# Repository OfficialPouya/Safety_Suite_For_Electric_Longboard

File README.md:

# Safety Suite For Electric Longboard
This is my Senior Design (ECE 445) Project

The goal of the project is to increase Safety for electric longboard users. To find out more about the project, feel free to watch the presentation, demos, and the rest of this repository. This project would not have been possible without the help of Alex and Patrick. 

Best Overall Project Winner (Spring 2021)
-----
Best project out of 72 teams/projects

$1500 Award

Contributors
-----
[Pouya Akbarzadeh](https://github.com/OfficialPouya)

[Alexander Krysl](https://github.com/axkrysl47)

[Patrick Stach](https://github.com/pat-stach) 

Demo
-----
[Demo Videos](https://www.youtube.com/playlist?list=PLA1k06jt2lX-8_wawuwcJB9zIEW_f2nJa)

Presentation
-----
[Brief Presentaion](https://www.youtube.com/watch?v=MWs525hmZTg)

Final Results
-----

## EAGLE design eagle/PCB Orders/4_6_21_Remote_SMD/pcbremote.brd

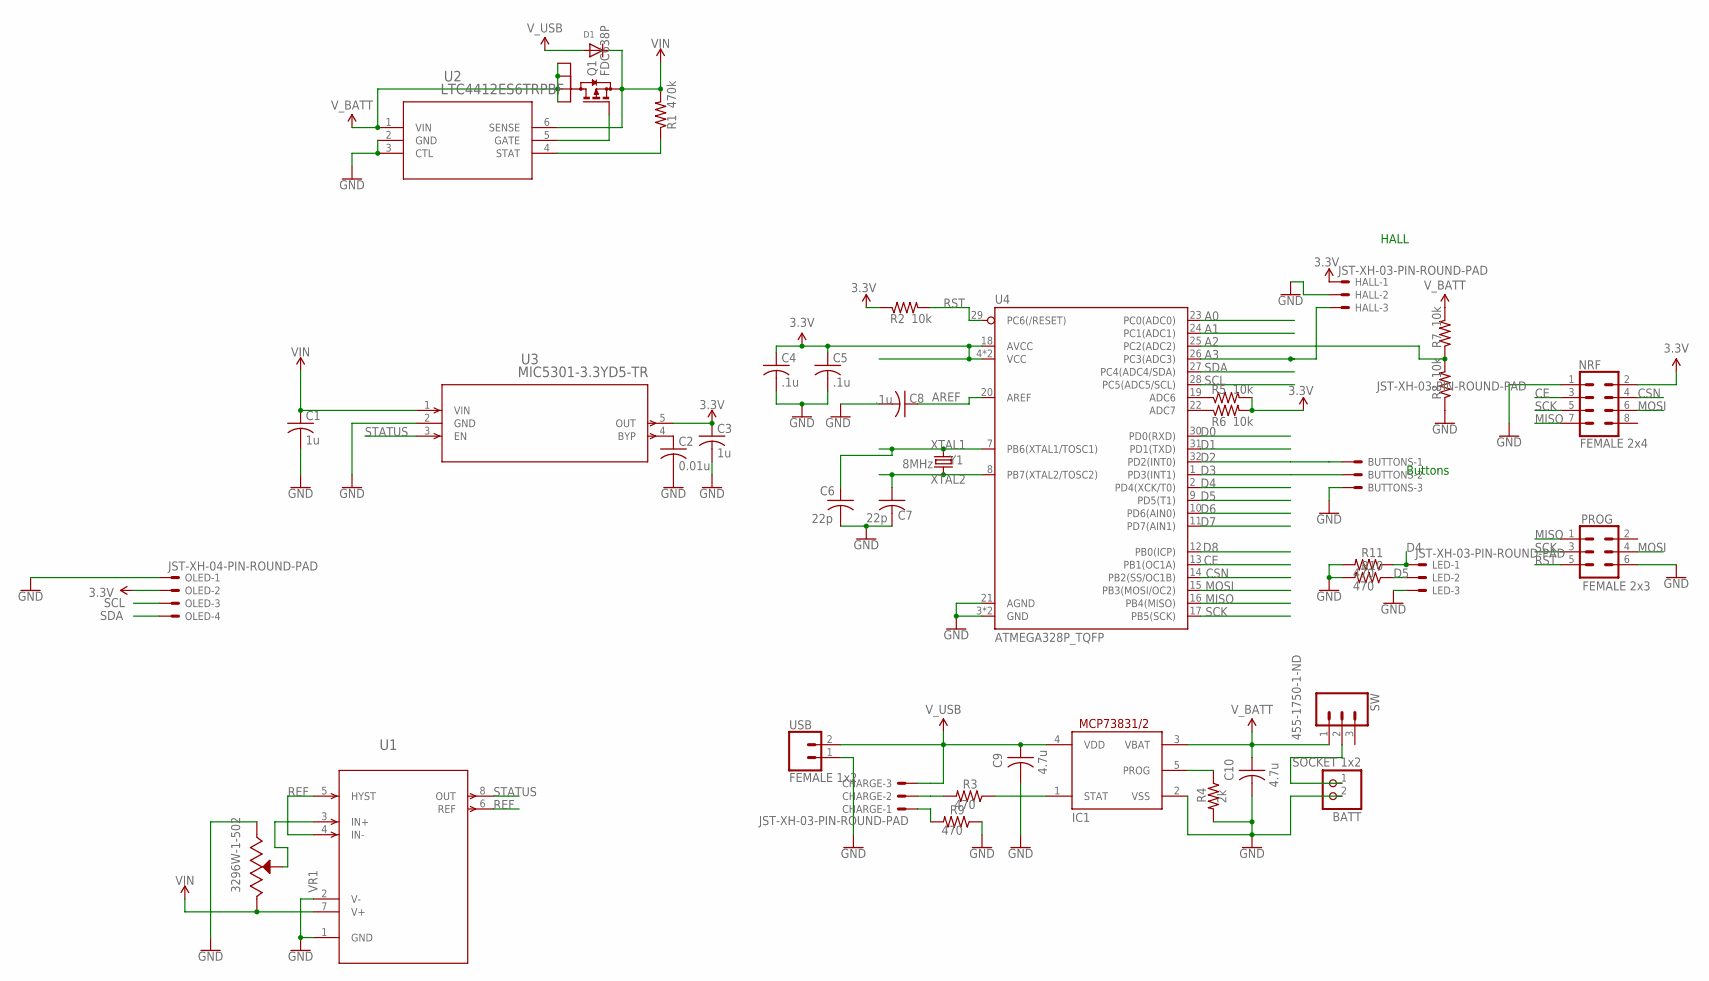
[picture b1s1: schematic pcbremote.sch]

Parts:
BATT: SOCKET 1x2; JST-PH-2-THM
BUTTONS: JST-XH-03-PIN-ROUND-PAD; JST-XH-03-PACKAGE-ROUND-PAD
C1, C3: 1u; C0805
C2: 0.01u; C0805
C4, C5, C8: .1u; C0805
C6, C7: 22p; C0805
C9, C10: 4.7u; C0805
CHARGE: JST-XH-03-PIN-ROUND-PAD; JST-XH-03-PACKAGE-ROUND-PAD
D1: DIODESOD-123; SOD-123
HALL: JST-XH-03-PIN-ROUND-PAD; JST-XH-03-PACKAGE-ROUND-PAD
IC1: MCP73831/OT; SOT23-5L
LED: JST-XH-03-PIN-ROUND-PAD; JST-XH-03-PACKAGE-ROUND-PAD
NRF: FEMALE 2x4; 2X4
OLED: JST-XH-04-PIN-ROUND-PAD; JST-XH-04-PACKAGE-ROUND-PAD
PROG: FEMALE 2x3; 2X3
Q1: FDC638P; SSOT-6
R1: 470k; R0805
R2, R5, R6, R7, R8: 10k; R0805
R3, R9, R10, R11: 470; R0805
R4: 2k; R0805
SW: 455-1750-1-ND; 1X03
U1: LTC1540CS8PBF; SO-8_S_LIT
U2: LTC4412ES6TRPBF; TSOT-23_S6_LIT
U3: MIC5301-3.3YD5-TR; TSOT-23-5_D5_MCH
U4: ATMEGA328P_TQFP; TQFP32-08
USB: FEMALE 1x2; 1X02
VR1: 3296W-1-502; TRIM_3296W-1-502
Y1: 8MHz; CRYSTAL-SMD-5X3.2-4PAD

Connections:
3.3V: C3.1, C4.1, C5.1, HALL.1, NRF.2, OLED.2, R2.1, R5.2, R6.2, U3.5 (OUT), U4.4 (VCC), U4.6 (VCC), U4.18 (AVCC)
A0: U4.23 (PC0(ADC0))
A1: U4.24 (PC1(ADC1))
A2: R7.1, R8.2, U4.25 (PC2(ADC2))
A3: HALL.3, U4.26 (PC3(ADC3))
AREF: C8.1, U4.20 (AREF)
CE: NRF.3, U4.13 (PB1(OC1A))
CSN: NRF.4, U4.14 (PB2(SS/OC1B))
D0: U4.30 (PD0(RXD))
D1: U4.31 (PD1(TXD))
D2: BUTTONS.1, U4.32 (PD2(INT0))
D3: BUTTONS.2, U4.1 (PD3(INT1))
D4: LED.1, R11.1, U4.2 (PD4(XCK/T0))
D5: LED.2, R10.1, U4.9 (PD5(T1))
D6: U4.10 (PD6(AIN0))
D7: U4.11 (PD7(AIN1))
D8: U4.12 (PB0(ICP))
GND: BATT.2 (1), BUTTONS.3, C1.2, C2.2, C3.2, C4.2, C5.2, C6.2, C7.2, C8.2, C9.2, C10.2, HALL.2, IC1.2 (VSS), LED.3, NRF.1, OLED.1, PROG.6, R4.2, R8.1, R9.1, R10.2, R11.2, U1.1 (GND), U1.2 (V-), U2.2 (GND), U2.3 (CTL), U3.2 (GND), U4.3 (GND), U4.5 (GND), U4.21 (AGND), USB.1, VR1.3 (CW)
MISO: NRF.7, PROG.1, U4.16 (PB4(MISO))
MOSI: NRF.6, PROG.4, U4.15 (PB3(MOSI/OC2))
unnamed: U1.3 (IN+), VR1.2 (WIPER)
unnamed: CHARGE.1, R9.2
unnamed: IC1.5 (PROG), R4.1
unnamed: IC1.1 (STAT), R3.1
unnamed: CHARGE.2, R3.2
unnamed: R5.1, U4.19 (ADC6)
unnamed: R6.1, U4.22 (ADC7)
unnamed: C2.1, U3.4 (BYP)
unnamed: Q1.3 (G), U2.5 (GATE)
unnamed: BATT.1 (2), SW.2
unnamed: R1.1, U2.4 (STAT)
REF: U1.4 (IN-), U1.5 (HYST), U1.6 (REF)
RST: PROG.5, R2.2, U4.29 (PC6(/RESET))
SCK: NRF.5, PROG.3, U4.17 (PB5(SCK))
SCL: OLED.3, U4.28 (PC5(ADC5/SCL))
SDA: OLED.4, U4.27 (PC4(ADC4/SDA))
STATUS: U1.8 (OUT), U3.3 (EN)
VIN: C1.1, D1.C, Q1.4 (S), R1.2, U1.7 (V+), U2.6 (SENSE), U3.1 (VIN), VR1.1 (CCW)
V_BATT: C10.1, IC1.3 (VBAT), Q1.1 (D4), Q1.2 (D1), Q1.5 (D2), Q1.6 (D3), R7.2, SW.1, U2.1 (VIN)
V_USB: C9.1, CHARGE.3, D1.A, IC1.4 (VDD), USB.2
XTAL1: C6.1, U4.7 (PB6(XTAL1/TOSC1)), Y1.1
XTAL2: C7.1, U4.8 (PB7(XTAL2/TOSC2)), Y1.3 (2)

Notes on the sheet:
Buttons
HALL

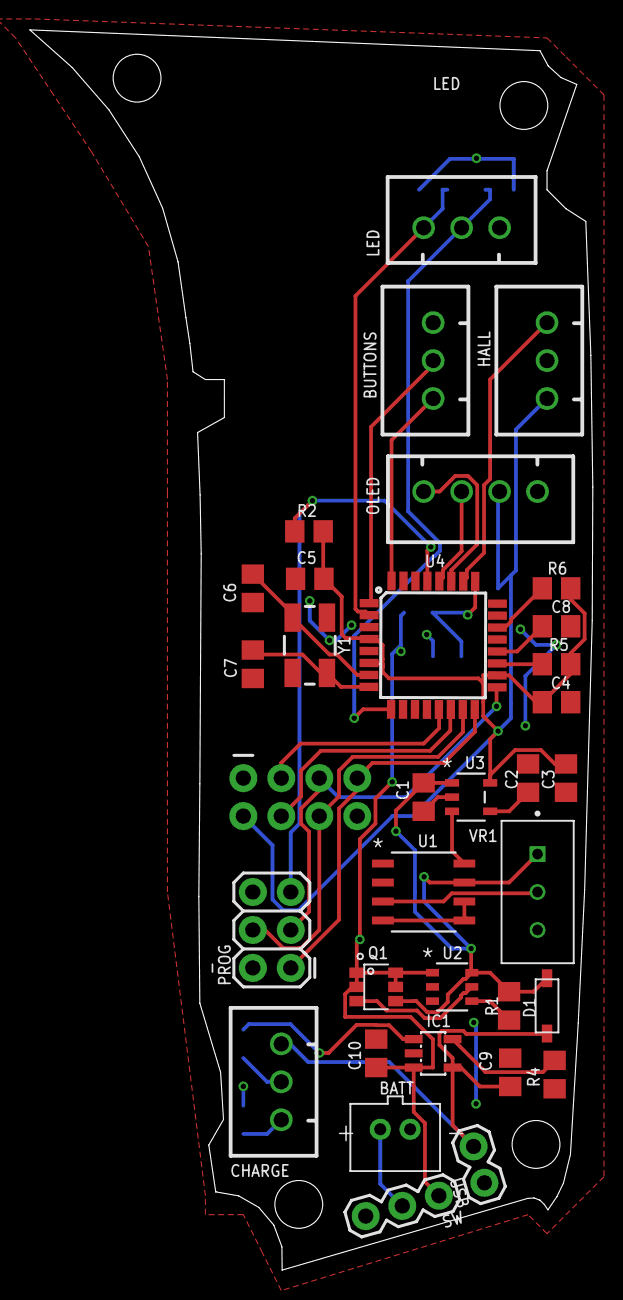
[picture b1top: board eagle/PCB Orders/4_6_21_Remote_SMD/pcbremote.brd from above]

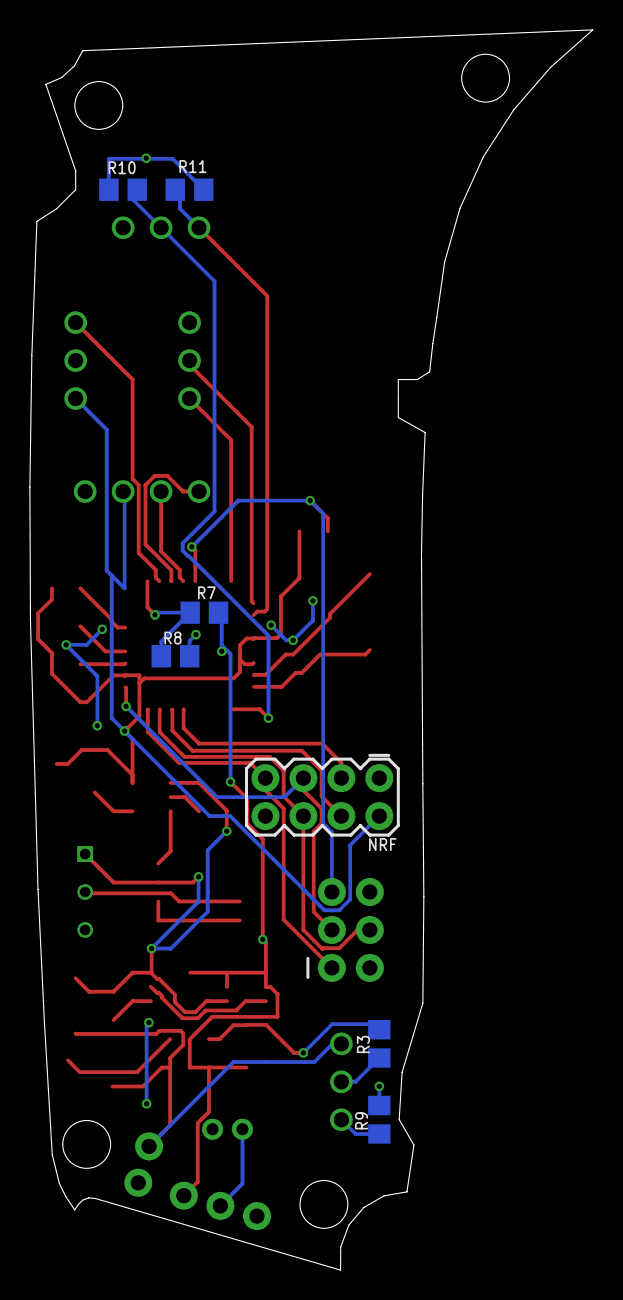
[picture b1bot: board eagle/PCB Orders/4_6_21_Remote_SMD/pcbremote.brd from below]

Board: 2 copper layers, 37.7 x 83.0 mm, 40 parts (7 on the bottom side), 35 nets.

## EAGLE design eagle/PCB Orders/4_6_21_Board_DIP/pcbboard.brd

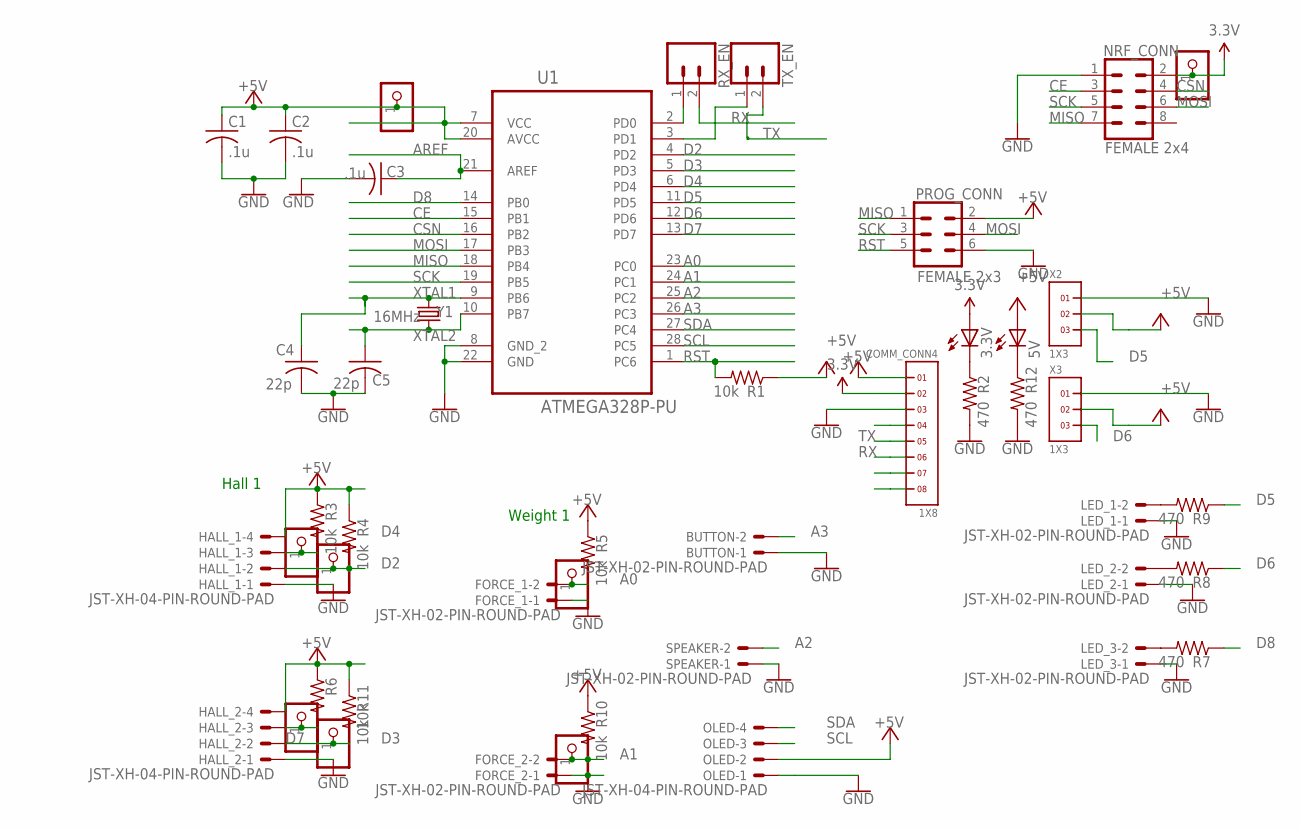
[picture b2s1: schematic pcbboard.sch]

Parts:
3.3V, 5V: LED3MM
BUTTON: JST-XH-02-PIN-ROUND-PAD; JST-XH-02-PACKAGE-ROUND-PAD
C1, C2, C3: .1u; C0805
C4, C5: 22p; C0805
COMM_CONN4: 1X8
FORCE_1, FORCE_2: JST-XH-02-PIN-ROUND-PAD; JST-XH-02-PACKAGE-ROUND-PAD
HALL_1, HALL_2: JST-XH-04-PIN-ROUND-PAD; JST-XH-04-PACKAGE-ROUND-PAD
LED_1, LED_2, LED_3: JST-XH-02-PIN-ROUND-PAD; JST-XH-02-PACKAGE-ROUND-PAD
NRF_CONN: FEMALE 2x4; 2X4
OLED: JST-XH-04-PIN-ROUND-PAD; JST-XH-04-PACKAGE-ROUND-PAD
PROG_CONN: FEMALE 2x3; 2X3
R1, R3, R4, R5, R6, R10, R11: 10k; R0805
R2, R7, R8, R9, R12: 470; R0805
RX_EN: CONN_02; 1X02
SPEAKER: JST-XH-02-PIN-ROUND-PAD; JST-XH-02-PACKAGE-ROUND-PAD
TP_3.3V, TP_5V: PINHD-1X1; 1X01
TP_F1, TP_F2: PINHD-1X1; 1X01
TP_H1-1, TP_H1-2, TP_H2-1, TP_H2-2: PINHD-1X1; 1X01
TX_EN: CONN_02; 1X02
U1: ATMEGA328P-PU; DIP254P762X457-28
X2, X3: 1X3
Y1: 16MHz; CRYSTAL-SMD-5X3.2-4PAD

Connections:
3.3V: 3.3V.A, COMM_CONN4.2, NRF_CONN.2, TP_3.3V.1
+5V: 5V.A, C1.1, C2.1, COMM_CONN4.1, HALL_1.4, HALL_2.4, OLED.2, PROG_CONN.2, R1.1, R3.1, R4.1, R5.1, R6.1, R10.1, R11.1, TP_5V.1, U1.7 (VCC), U1.20 (AVCC), X2.2, X3.2
A0: FORCE_1.2, R5.2, TP_F1.1, U1.23 (PC0)
A1: FORCE_2.2, R10.2, TP_F2.1, U1.24 (PC1)
A2: SPEAKER.2, U1.25 (PC2)
A3: BUTTON.2, U1.26 (PC3)
AREF: C3.1, U1.21 (AREF)
CE: NRF_CONN.3, U1.15 (PB1)
CSN: NRF_CONN.4, U1.16 (PB2)
D2: HALL_1.2, R4.2, TP_H1-2.1, U1.4 (PD2)
D3: HALL_2.2, R11.2, TP_H2-2.1, U1.5 (PD3)
D4: HALL_1.3, R3.2, TP_H1-1.1, U1.6 (PD4)
D5: R9.1, U1.11 (PD5), X2.3
D6: R8.1, U1.12 (PD6), X3.3
D7: HALL_2.3, R6.2, TP_H2-1.1, U1.13 (PD7)
D8: R7.1, U1.14 (PB0)
GND: BUTTON.1, C1.2, C2.2, C3.2, C4.2, C5.2, COMM_CONN4.3, FORCE_1.1, FORCE_2.1, HALL_1.1, HALL_2.1, LED_1.1, LED_2.1, LED_3.1, NRF_CONN.1, OLED.1, PROG_CONN.6, R2.2, R12.2, SPEAKER.1, U1.8 (GND_2), U1.22 (GND), X2.1, X3.1
MISO: NRF_CONN.7, PROG_CONN.1, U1.18 (PB4)
MOSI: NRF_CONN.6, PROG_CONN.4, U1.17 (PB3)
unnamed: LED_3.2, R7.2
unnamed: LED_2.2, R8.2
unnamed: LED_1.2, R9.2
unnamed: 3.3V.K (C), R2.1
unnamed: 5V.K (C), R12.1
unnamed: RX_EN.1, U1.2 (PD0)
unnamed: TX_EN.1, U1.3 (PD1)
RST: PROG_CONN.5, R1.2, U1.1 (PC6)
RX: COMM_CONN4.6, RX_EN.2
SCK: NRF_CONN.5, PROG_CONN.3, U1.19 (PB5)
SCL: OLED.3, U1.28 (PC5)
SDA: OLED.4, U1.27 (PC4)
TX: COMM_CONN4.5, TX_EN.2
XTAL1: C4.1, U1.9 (PB6), Y1.1
XTAL2: C5.1, U1.10 (PB7), Y1.3 (2)

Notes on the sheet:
Hall 1
Weight 1

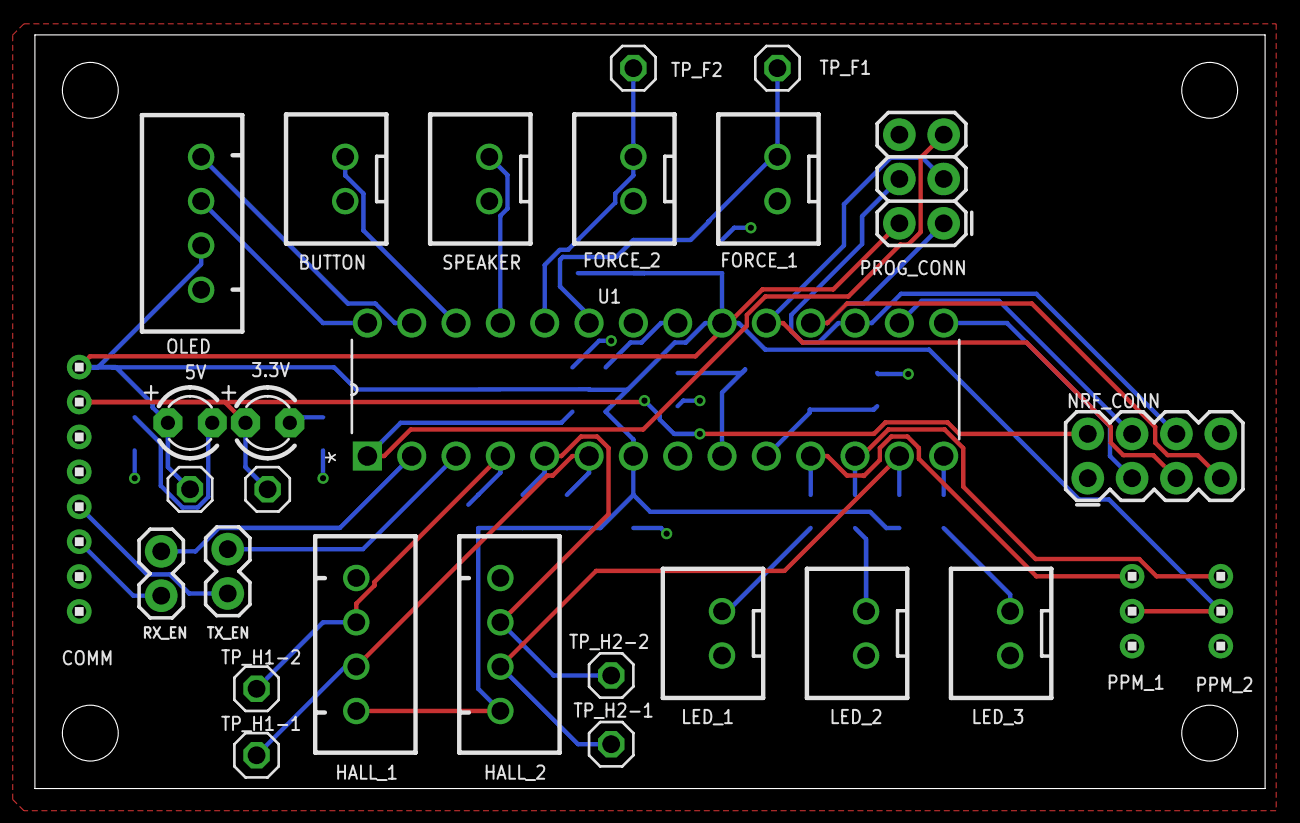
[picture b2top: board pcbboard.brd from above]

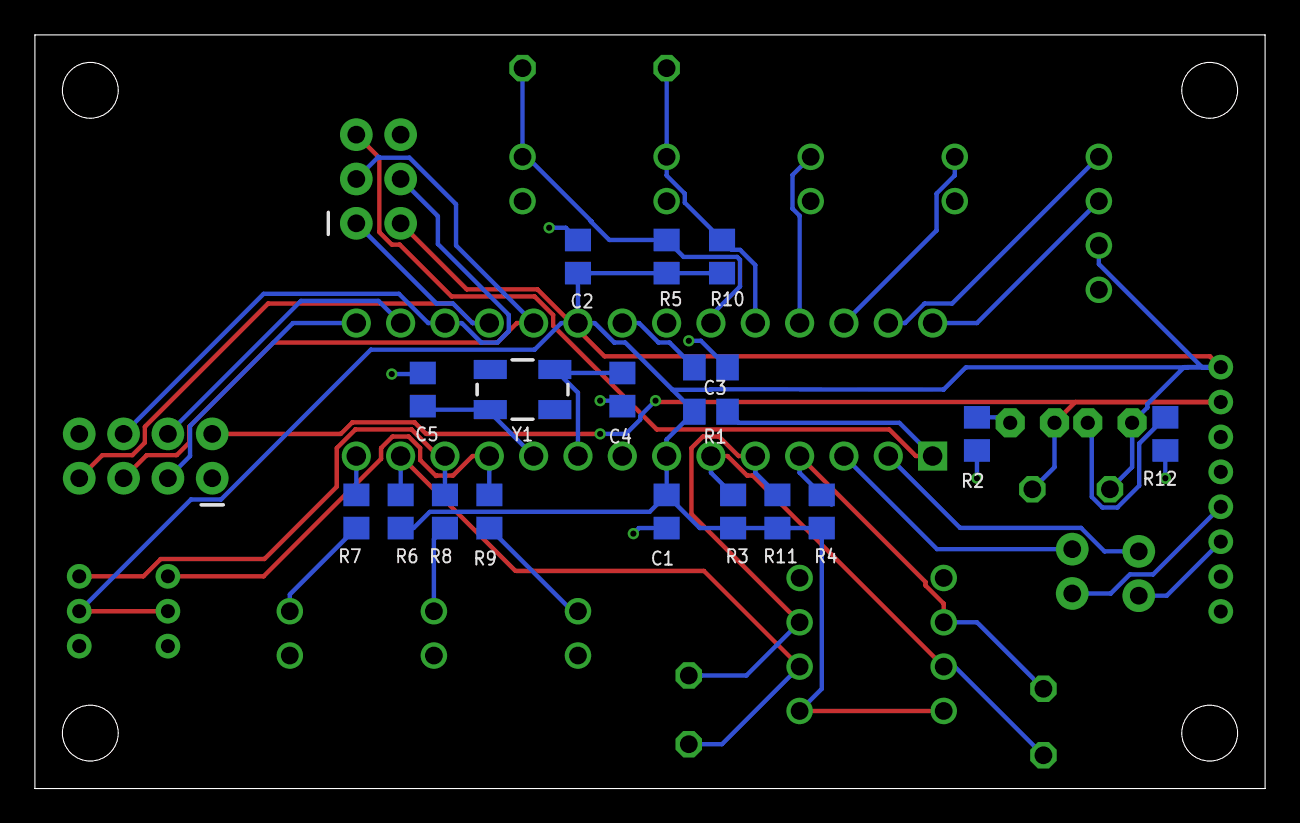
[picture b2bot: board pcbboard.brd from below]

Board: 2 copper layers, 70.5 x 43.2 mm, 46 parts (18 on the bottom side), 34 nets.

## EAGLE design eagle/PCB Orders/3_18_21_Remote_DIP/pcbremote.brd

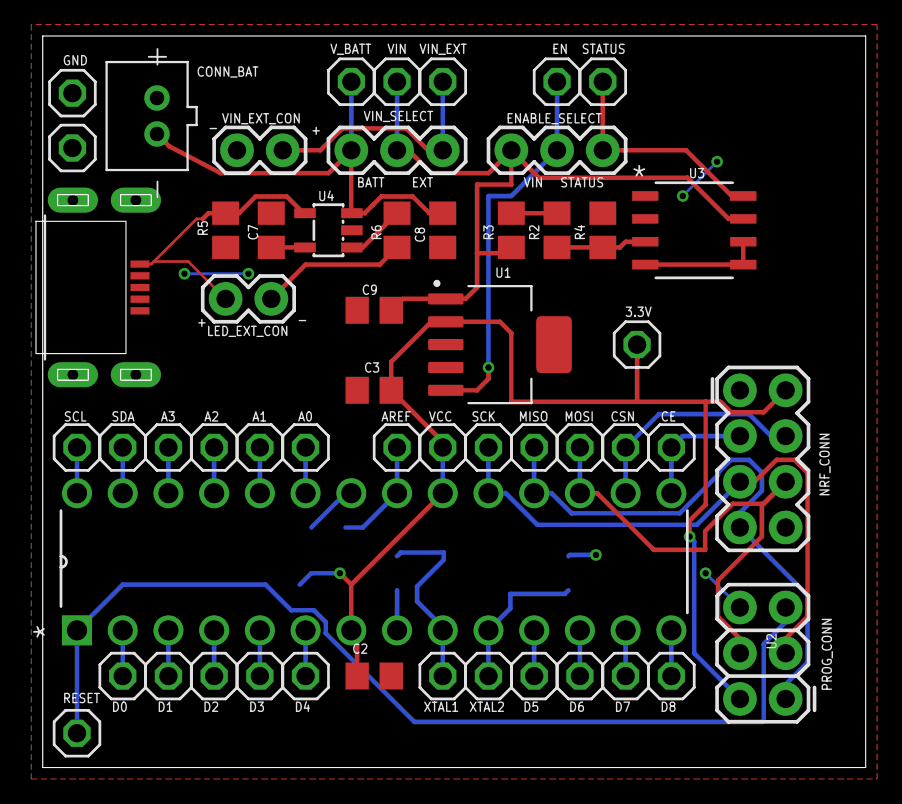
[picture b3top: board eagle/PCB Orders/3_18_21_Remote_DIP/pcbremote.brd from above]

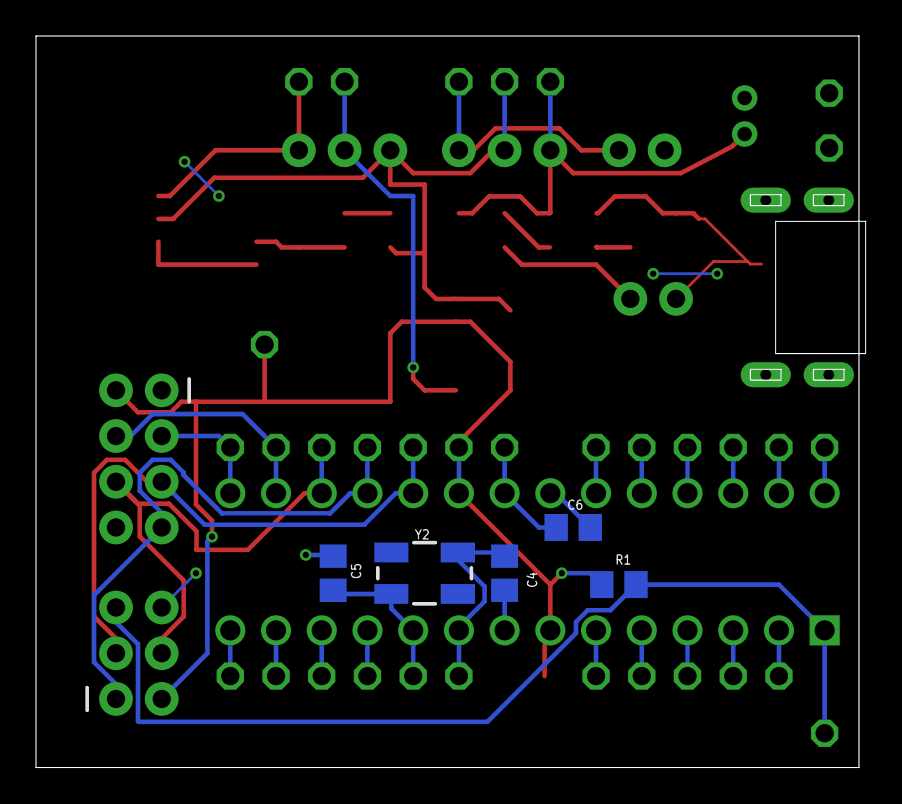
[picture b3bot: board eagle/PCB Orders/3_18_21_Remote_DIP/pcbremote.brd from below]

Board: 2 copper layers, 46.1 x 40.6 mm, 60 parts (5 on the bottom side), 38 nets.

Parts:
3.3V: 1X01
A0, A1, A2, A3: 1X01
AREF: 1X01
C2, C3, C6: .1u; C0805
C4, C5: 22p; C0805
C7, C8: 4.7u; C0805
C9: 10u; C0805
CE: 1X01
CONN_BAT: SOCKET 1x2; JST-PH-2-THM
CSN: 1X01
D0, D1, D2, D3, D4, D5, D6, D7, D8: 1X01
EN: 1X01
ENABLE_SELECT: MALE 1x3; 1X03
GND, GND7: 1X01
LED_EXT_CON: FEMALE 1x2; 1X02
MISO: 1X01
MOSI: 1X01
NRF_CONN: FEMALE 2x4; 2X4
PROG_CONN: FEMALE 2x3; 2X3
R1: 10k; R0805
R2: 2.26Meg; R0805
R3: 0; R0805
R4: 1.18Meg; R0805
R5: 2k; R0805
R6: 470; R0805
RESET: 1X01
SCK: 1X01
SCL: 1X01
SDA: 1X01
STATUS: 1X01
U1: TPS73233DCQR; SOT127P706X180-6N
U2: ATMEGA328P-PU; DIP254P762X457-28
U3: LTC1540CS8PBF; SO-8_S_LIT
U4: MCP73831/OT; SOT23-5L
USB: MICRO-USBV2; MICRO-USB-2
VCC: 1X01
VIN: 1X01
VIN_EXT: 1X01
VIN_EXT_CON: FEMALE 1x2; 1X02
VIN_SELECT: MALE 1x3; 1X03
V_BATT: 1X01
XTAL1, XTAL2: 1X01
Y2: 8MHz; CRYSTAL-SMD-5X3.2-4PAD

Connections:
3.3V: 3.3V.1, C2.1, C3.1, NRF_CONN.2, PROG_CONN.2, R1.1, U1.2, U2.7, U2.20, VCC.1
A0: A0.1, U2.23
A1: A1.1, U2.24
A2: A2.1, U2.25
A3: A3.1, U2.26
AREF: AREF.1, C6.1, U2.21
CE: CE.1, NRF_CONN.3, U2.15
CSN: CSN.1, NRF_CONN.4, U2.16
D0: D0.1, U2.2
D1: D1.1, U2.3
D2: D2.1, U2.4
D3: D3.1, U2.5
D4: D4.1, U2.6
D5: D5.1, U2.11
D6: D6.1, U2.12
D7: D7.1, U2.13
D8: D8.1, U2.14
GND: C2.2, C3.2, C4.2, C5.2, C6.2, C7.2, C8.2, C9.2, CONN_BAT.1, GND.1, GND7.1, NRF_CONN.1, PROG_CONN.6, R4.1, R5.2, U1.3, U1.6, U2.8, U2.22, U3.1, U3.2, U4.2, USB.5, USB.P$1, USB.P$2, USB.P$3, USB.P$4, VIN_EXT_CON.1
MISO: MISO.1, NRF_CONN.7, PROG_CONN.1, U2.18
MOSI: MOSI.1, NRF_CONN.6, PROG_CONN.4, U2.17
unnamed: R2.2, R4.2, U3.3
unnamed: R2.1, R3.1
unnamed: R5.1, U4.5
unnamed: R6.1, U4.1
unnamed: LED_EXT_CON.1, R6.2
unnamed: EN.1, ENABLE_SELECT.2, U1.5
REF: U3.4, U3.5, U3.6
RST: PROG_CONN.5, R1.2, RESET.1, U2.1
SCK: NRF_CONN.5, PROG_CONN.3, SCK.1, U2.19
SCL: SCL.1, U2.28
SDA: SDA.1, U2.27
STATUS: ENABLE_SELECT.1, STATUS.1, U3.8
VIN: C9.1, ENABLE_SELECT.3, R3.2, U1.1, U3.7, VIN.1, VIN_SELECT.2
V_BATT: C8.1, CONN_BAT.2, U4.3, VIN_SELECT.1, V_BATT.1
V_EXT: VIN_EXT.1, VIN_EXT_CON.2, VIN_SELECT.3
V_USB: C7.1, LED_EXT_CON.2, U4.4, USB.1
XTAL1: C4.1, U2.9, XTAL1.1, Y2.1
XTAL2: C5.1, U2.10, XTAL2.1, Y2.3

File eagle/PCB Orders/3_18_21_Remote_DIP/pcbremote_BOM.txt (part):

Partlist exported from C:/Users/Patrick/Documents/GitHub/senior_design/eagle/PCB Orders/3_18_21_Remote_DIP/pcbremote.sch at 4/3/2021 3:05 PM

Part          Value         Device                Package                Description                                                                                                     BUILT_BY    DESCRIPTION                                                                                                                DIGI-KEY_PART_NUMBER MANUFACTURER_PART_NUMBER MF                MP           MPN           OC_FARNELL OC_NEWARK PACKAGE                     POPULARITY PROD_ID    PURCHASE-URL                                                  SOURCELIBRARY         SPICEPREFIX SUPPLIER VALUE         VENDOR           
3.3V                        PINHD-1X1             1X01                   PIN HEADER                                                                                                                                                                                                                                                                                                                                                                                         64                                                                                                                                                            
A0                          PINHD-1X1             1X01                   PIN HEADER                                                                                                                                                                                                                                                                                                                                                                                         64                                                                                                                                                            
A1                          PINHD-1X1             1X01                   PIN HEADER                                                                                                                                                                                                                                                                                                                                                                                         64                                                                                                                                                            
A2                          PINHD-1X1             1X01                   PIN HEADER                                                                                                                                                                                                                                                                                                                                                                                         64                                                                                                                                                            
A3                          PINHD-1X1             1X01                   PIN HEADER                                                                                                                                                                                                                                                                                                                                                                                         64                                                                                                                                                            
AREF                        PINHD-1X1             1X01                   PIN HEADER                                                                                                                                                                                                                                                                                                                                                                                         64                                                                                                                                                            
C2            .1u           C-USC0805             C0805                  CAPACITOR, American symbol                                                                                                                                                                                                                                                                                                                                                                         63                                                                                                        C                                                   
C3            .1u           C-USC0805             C0805                  CAPACITOR, American symbol                                                                                                                                                                                                                                                                                                                                                                         63                                                                                                        C                                                   
C4            22p           C-USC0805             C0805                  CAPACITOR, American symbol                                                                                                                                                                                                                                                                                                                                                                         63                                                                                                        C                                                   
C5            22p           C-USC0805             C0805                  CAPACITOR, American symbol                                                                                                                                                                                                                                                                                                                                                                         63                                                                                                        C                                                   
C6            .1u           C-USC0805             C0805                  CAPACITOR, American symbol                                                                                                                                                                                                                                                                                                                                                                         63                                                                                                        C                                                   
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
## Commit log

2021-01-29 Create info
2021-01-31 Initialize Documentation
2021-01-31 Update info
2021-03-01 Added to github
2021-03-02 adding digital_comm_sending
2021-03-02 adding digital read code
2021-03-02 LED corresponding payload
2021-03-03 Able to read values from nunchuck
2021-03-07 got 2 way comm working
2021-03-07 code for board comms with remote done
2021-03-07 added remote comm to board
2021-03-07 added code receipt from board to controller
2021-03-14 added timing code
2021-03-15 updated timing for board
2021-03-22 PCB Files for Remote 1st PCB Order
2021-03-25 Change PCB Stuff, add ipt
2021-03-25 Import remote layer
2021-03-25 Add Remote Shape
2021-03-25 Snapped to grid
2021-03-25 Pre-airwire, everything labeled
2021-03-25 Airwire no gnd
2021-03-25 Added mounting holes and routing spots
2021-03-25 Parts print 3_25
2021-03-26 Update Hall 3 pin
2021-03-26 Changed spacing to 60+15 degrees for hall mount, only two now
2021-03-26 wheel allignment thing = hole diameter - .5mm
2021-03-28 Not fully working
2021-03-28 not working
2021-03-28 updating code
2021-03-29 Added trucks
2021-03-29 changed truck mount thickness from .2 in to .1 in
2021-03-29 retreat: 4.3mm->4.5mm
2021-03-29 modify shell heated inserts
2021-03-29 Cleaning GIT
2021-03-29 Basic Comm Test ADDED
2021-03-29 shell_no_attach 4.2mm holes and usb c cutout
2021-03-29 added 1 way comms
2021-03-29 updating remote 1way code
2021-03-29 1way
2021-03-30 updated for testing 1way
2021-03-30 pin mismatch
2021-03-30 initial 2way code
2021-03-30 value fixes. 2way with ack fully works
2021-03-30 2 Way Comms Fully Working
2021-03-30 added comments, function headers, and made loop just call functions
2021-03-31 test 4.3->4.35, 4.4mm, thicker switch
2021-03-31 add switch holder for remote
2021-04-01 switch- added bearing cutout, reversed direction
2021-04-01 modified shell to include switch mount, scroll wheel 32->31.5
2021-04-02 switch cutout got rid of extra on edge
2021-04-02 cut away edges of knob .5mm, made holes a bit bigger
2021-04-04 added hall effect
2021-04-06 Add ext interrupt hall sense
2021-04-06 fixing RPM
2021-04-06 Add PCB board for round 3 order
2021-04-06 Board 3 Rev first steps
2021-04-06 More Revisions
2021-04-06 Re organized board
2021-04-06 CLeaned up layout board
2021-04-06 Done but need to reroute
2021-04-06 Remote almost finish
2021-04-06 PCB DOne
2021-04-08 added code for basic hardware test
2021-04-09 added rpm code
2021-04-09 bigger oled code
2021-04-09 small oled code added
2021-04-09 rpm reading fixed, code cleaned up, needs more comments
2021-04-12 lite version added
2021-04-19 added_test_code
2021-04-19 board and remote v3 working
2021-04-19 added buzzer for slip and eject and loss of connection detection
2021-04-19 made buzzers not buzz as long
2021-04-19 cleaning up git
2021-04-19 board speaker implemented
2021-04-19 hall effect range help
2021-04-19 remote test now can be monitored
    corrected pins for remote to match final product. Decreased transmission delay. added code to monitor rpm from wirelessly.
2021-04-19 adding monitor code
2021-04-19 debug line removed
2021-04-20 updated with new throttle val
2021-04-21 Restructure, Knob_With_Bearing_Middle_Hole
    Knob_With_Bearing_Middle_Hole- Modified with magnet cutout for middle hole. Holes now go all the way
2021-04-21 Restructure
    Knob_With_Bearing_Middle_Hole.ipt-
    Just_Hall_Holder.ipt- Hall Sensor Holder Only
    Switch_Thick.ipt - Switch Used for most recent built
    Shell_Bottom.ipt - Bottom Shell
2021-04-21 Shell_Bottom.ipt
    Shell_Bottom.ipt- Update w/ original switch mount
2021-04-21 Just_Hall_Holder.ipt: 7.8mm->6mm
2021-04-22 PCB_BOARD_Holder_.ipt, USB_MOUNT
    PCB_BOARD_Holder_.ipt: Used non dremel hole print and add heated insert hole
    USB_MOUNT.ipt: adjust for pcb thickness
2021-04-24 warning code sounds
2021-04-28 shell_top_USB_JUST_holder.ipt
    Cutout remote, holes 1.15->1.5mm
2021-04-28 shell_top_USB_just_holder
    .15in to .135 in
2021-04-29 added 3d models, pcbs from pats branch to main
2021-04-29 Organized GIT
2021-04-29 Add long boi big screen
2021-05-17 added documentation
2021-05-17 name updates
2021-05-21 added personal half way report

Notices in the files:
parts and their libraries:
SparkFun-Connectors: Licensing: Creative Commons ShareAlike 4.0 International - https://creativecommons.org/licenses/by-sa/4.0
COPYRIGHT: Copyright (C) 2018 Accelerated Designs. All rights reserved
